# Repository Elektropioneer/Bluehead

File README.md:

# Bluehead
Bluehead - STM32 main board

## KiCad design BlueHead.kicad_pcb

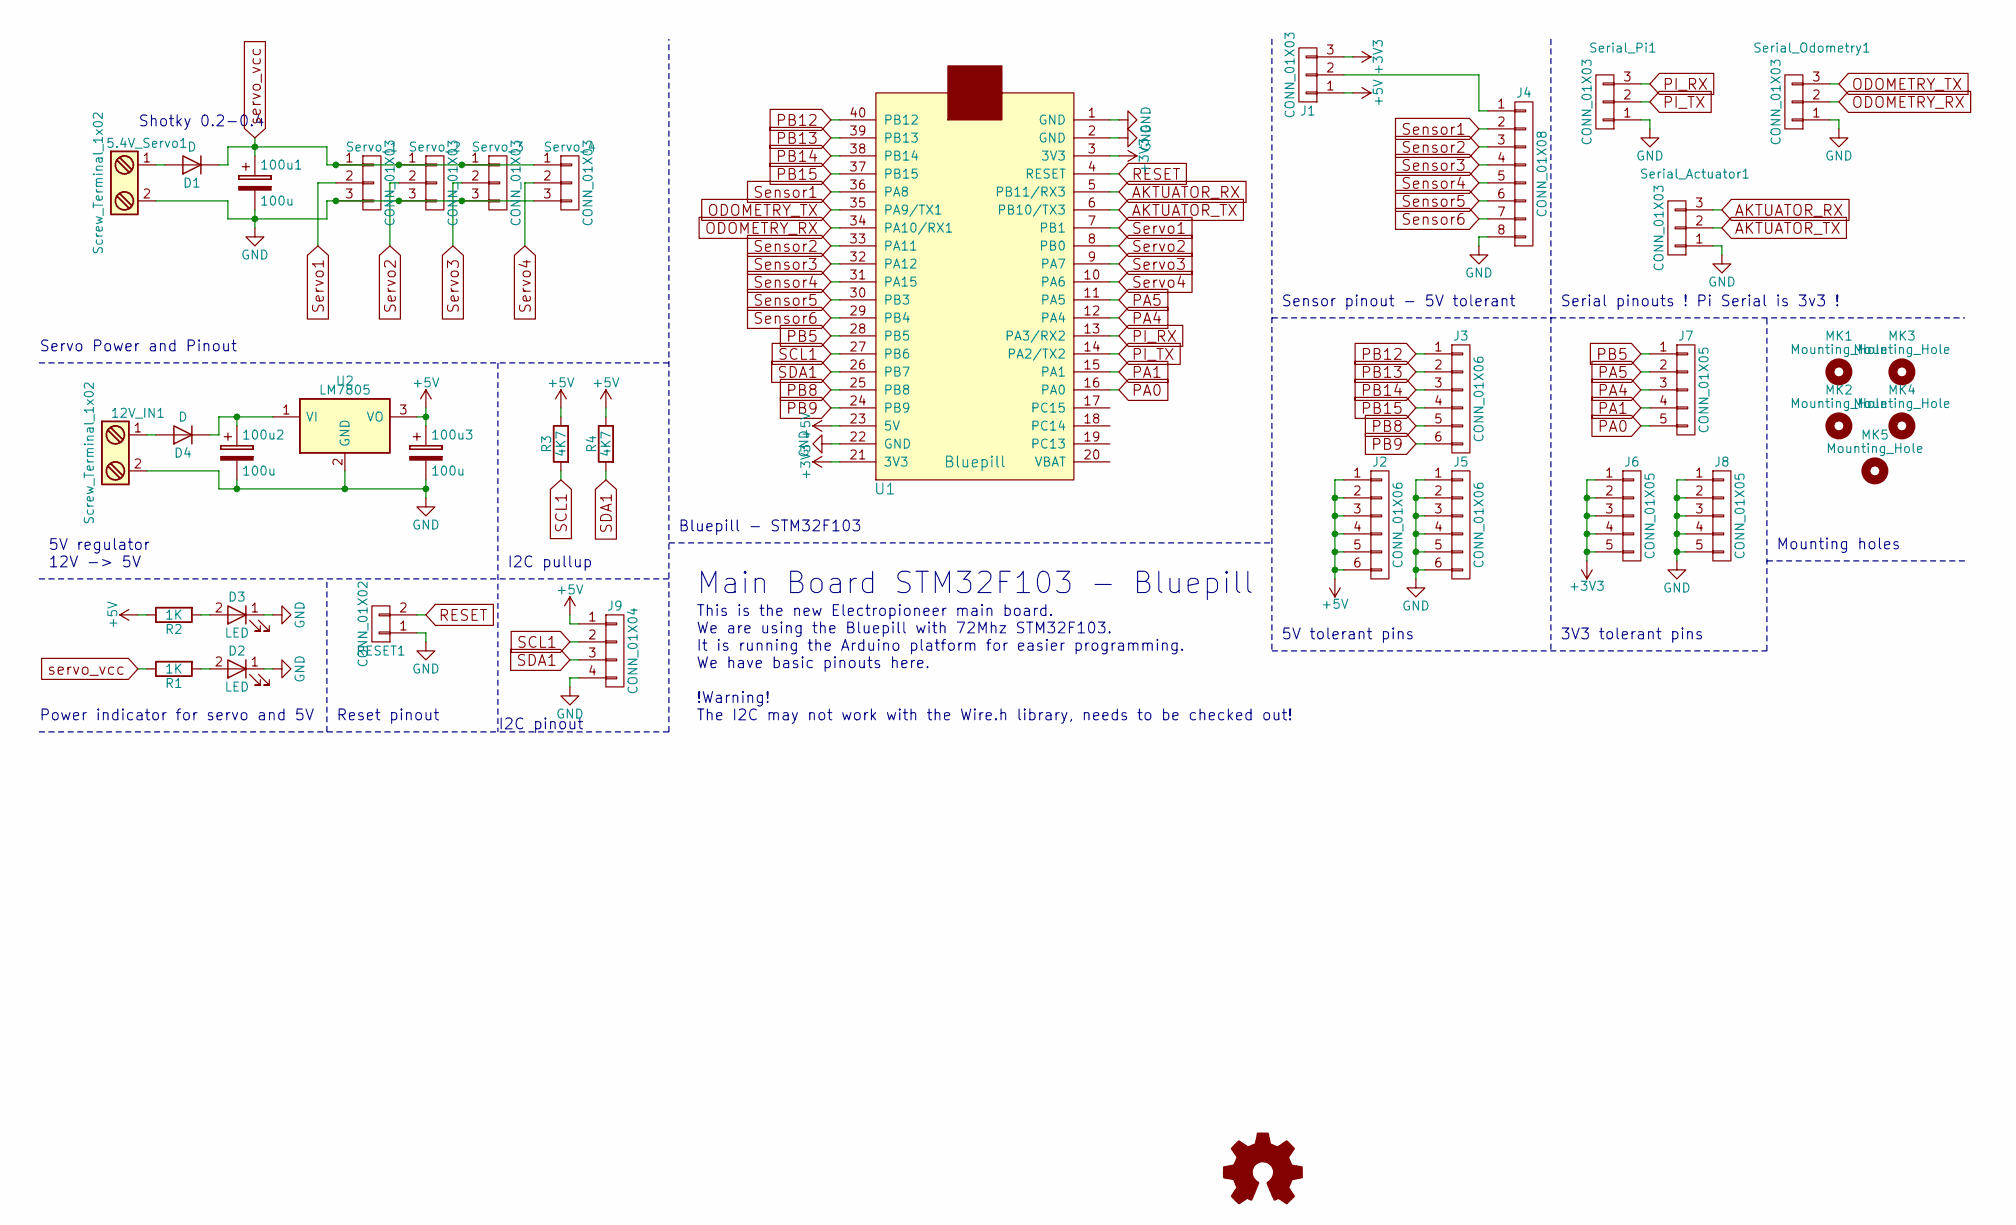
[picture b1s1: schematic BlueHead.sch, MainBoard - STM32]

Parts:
5.4V_Servo1, 12V_IN1: Screw_Terminal_1x02; TerminalBlock_Pheonix_MKDS1.5-2pol
100u1, 100u2, 100u3: 100u; CP_Elec_6.3x5.3
D1, D4: D; D_SMA_Standard
D2, D3: LED; LED_0805
J1: CONN_01X03; Pin_Header_Straight_1x03_Pitch2.54mm
J2, J3, J5: CONN_01X06; Pin_Header_Straight_1x06_Pitch2.54mm
J4: CONN_01X08; Pin_Header_Straight_1x08_Pitch2.54mm
J6, J7, J8: CONN_01X05; Pin_Header_Straight_1x05_Pitch2.54mm
J9: CONN_01X04; Pin_Header_Straight_1x04_Pitch2.54mm
LOGO1: OPEN_HARDWARE_1
MK1, MK2, MK3, MK4, MK5: Mounting_Hole; MountingHole_3.2mm_M3_Pad_Via
R1, R2: 1K; R_0805
R3, R4: 4K7; R_0805
RESET1: CONN_01X02; Pin_Header_Straight_1x02_Pitch2.54mm
Serial_Actuator1: CONN_01X03; Pin_Header_Straight_1x03_Pitch2.54mm
Serial_Odometry1: CONN_01X03; Pin_Header_Straight_1x03_Pitch2.54mm
Serial_Pi1: CONN_01X03; Pin_Header_Straight_1x03_Pitch2.54mm
Servo_1, Servo_2, Servo_3, Servo_4: CONN_01X03; Pin_Header_Straight_1x03_Pitch2.54mm
U1: Bluepill
U2: LM7805; TO-252-2Lead

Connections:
+3V3: J1.3, J6.1, J6.2, J6.3, J6.4, J6.5, U1.3 (3V3), U1.21 (3V3)
+5V: 100u3.1, J1.1, J2.1, J2.2, J2.3, J2.4, J2.5, J2.6, J9.1, R2.1, R3.1, R4.1, U1.23 (5V), U2.3 (VO)
AKTUATOR_RX: Serial_Actuator1.3, U1.5 (PB11/RX3)
AKTUATOR_TX: Serial_Actuator1.2, U1.6 (PB10/TX3)
GND: 5.4V_Servo1.2, 12V_IN1.2, 100u1.2, 100u2.2, 100u3.2, D2.1 (K), D3.1 (K), J4.8, J5.1, J5.2, J5.3, J5.4, J5.5, J5.6, J8.1, J8.2, J8.3, J8.4, J8.5, J9.4, RESET1.1, Serial_Actuator1.1, Serial_Odometry1.1, Serial_Pi1.1, Servo_1.3, Servo_2.3, Servo_3.3, Servo_4.3, U1.1 (GND), U1.2 (GND), U1.22 (GND), U2.2 (GND)
unnamed: 5.4V_Servo1.1, D1.2 (A)
unnamed: 12V_IN1.1, D4.2 (A)
unnamed: 100u2.1, D4.1 (K), U2.1 (VI)
unnamed: D2.2 (A), R1.2
unnamed: D3.2 (A), R2.2
unnamed: J1.2, J4.1
ODOMETRY_RX: Serial_Odometry1.2, U1.34 (PA10/RX1)
ODOMETRY_TX: Serial_Odometry1.3, U1.35 (PA9/TX1)
PA0: J7.5, U1.16 (PA0)
PA1: J7.4, U1.15 (PA1)
PA4: J7.3, U1.12 (PA4)
PA5: J7.2, U1.11 (PA5)
PB5: J7.1, U1.28 (PB5)
PB8: J3.5, U1.25 (PB8)
PB9: J3.6, U1.24 (PB9)
PB12: J3.1, U1.40 (PB12)
PB13: J3.2, U1.39 (PB13)
PB14: J3.3, U1.38 (PB14)
PB15: J3.4, U1.37 (PB15)
PI_RX: Serial_Pi1.3, U1.13 (PA3/RX2)
PI_TX: Serial_Pi1.2, U1.14 (PA2/TX2)
RESET: RESET1.2, U1.4 (RESET)
SCL1: J9.2, R3.2, U1.27 (PB6)
SDA1: J9.3, R4.2, U1.26 (PB7)
Sensor1: J4.2, U1.36 (PA8)
Sensor2: J4.3, U1.33 (PA11)
Sensor3: J4.4, U1.32 (PA12)
Sensor4: J4.5, U1.31 (PA15)
Sensor5: J4.6, U1.30 (PB3)
Sensor6: J4.7, U1.29 (PB4)
Servo1: Servo_1.2, U1.7 (PB1)
Servo2: Servo_2.2, U1.8 (PB0)
Servo3: Servo_3.2, U1.9 (PA7)
Servo4: Servo_4.2, U1.10 (PA6)
servo_vcc: 100u1.1, D1.1 (K), R1.1, Servo_1.1, Servo_2.1, Servo_3.1, Servo_4.1

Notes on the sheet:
Shotky 0.2-0.4
Servo Power and Pinout
5V regulator 12V -> 5V
Power indicator for servo and 5V
Reset pinout
Bluepill - STM32F103
Sensor pinout - 5V tolerant
Serial pinouts ! Pi Serial is 3v3 !
5V tolerant pins
3V3 tolerant pins
Mounting holes
I2C pinout
Main Board STM32F103 - Bluepill
This is the new Electropioneer main board. We are using the Bluepill with 72Mhz STM32F103. It is running the Arduino platform for easier programming. We have basic pinouts here. !Warning! The I2C may not work with the Wire.h library, needs to be checked out!
I2C pullup

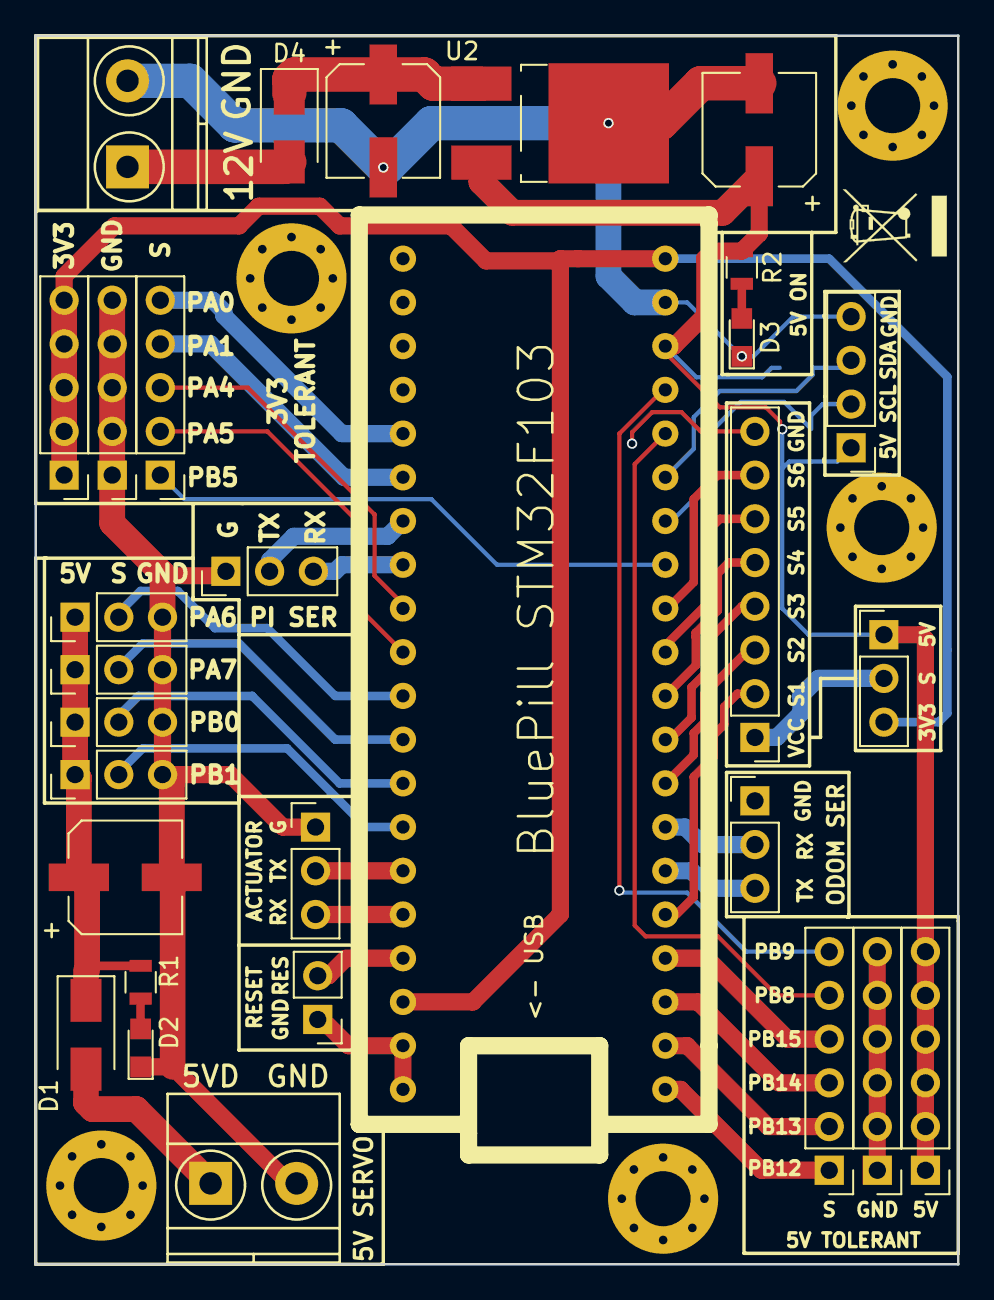
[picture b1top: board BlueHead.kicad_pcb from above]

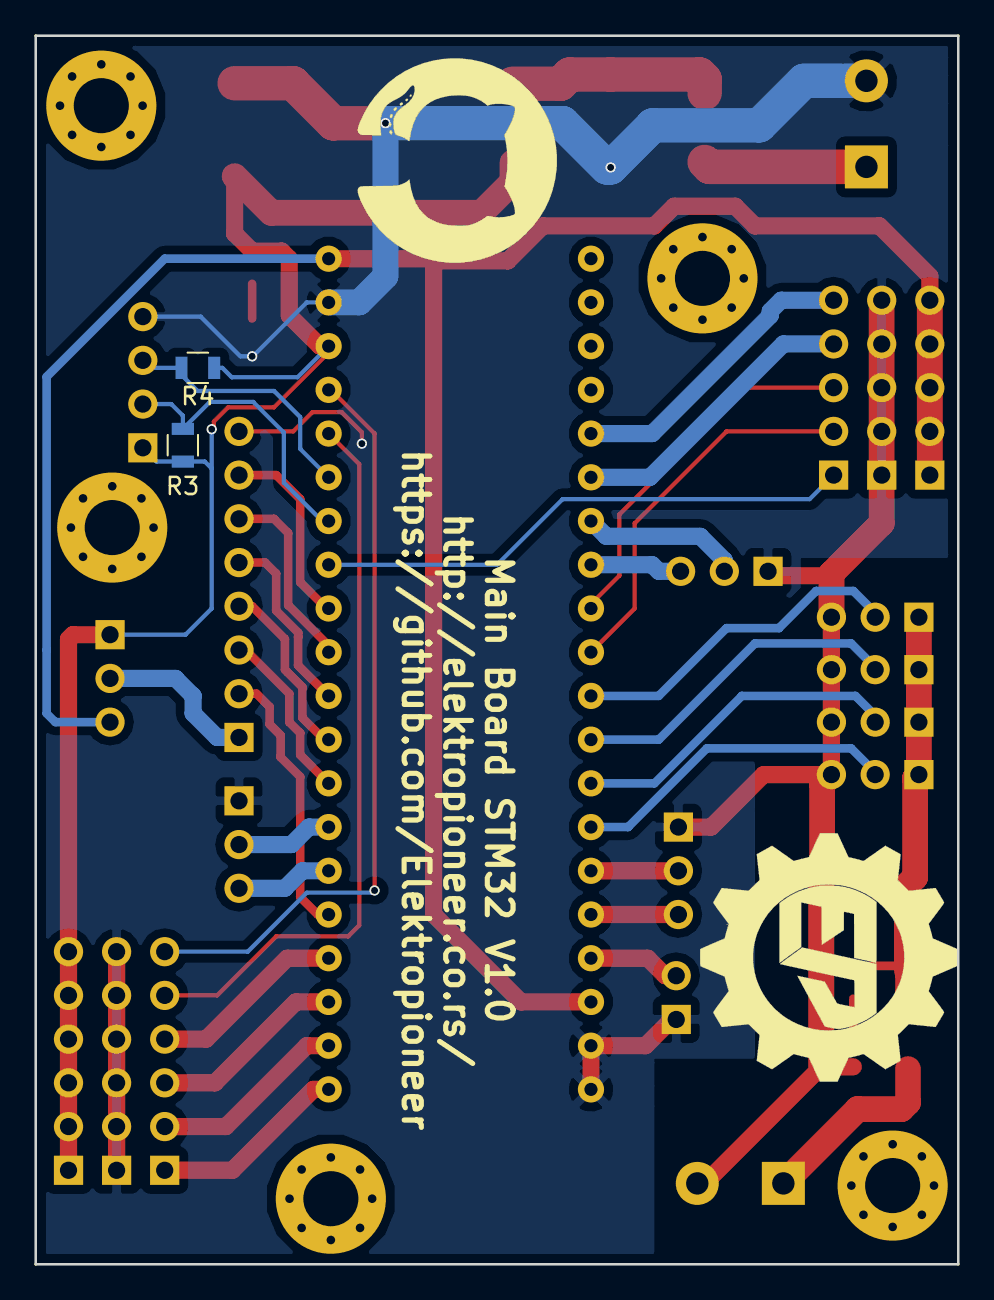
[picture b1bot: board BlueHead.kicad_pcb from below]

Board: 2 copper layers, 53.6 x 71.4 mm, 37 parts (2 on the bottom side), 40 nets.

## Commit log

2018-02-10 Main files
2018-02-10 Added outputs
2018-02-14 Issue resolving
2018-02-26 Plot
2018-02-26 Added mask
